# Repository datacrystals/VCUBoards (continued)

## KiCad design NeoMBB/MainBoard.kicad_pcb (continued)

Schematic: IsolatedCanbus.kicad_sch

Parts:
C44, C50, C51, C53: 100nF; C_1210_3225Metric_Pad1.33x2.70mm_HandSolder
C45, C49: 22pF; C_1210_3225Metric_Pad1.33x2.70mm_HandSolder
C46, C47, C48, C52: 10uF; C_1210_3225Metric_Pad1.33x2.70mm_HandSolder
C54, C55, C56: 22pF; C_1210_3225Metric_Pad1.33x2.70mm_HandSolder; not fitted
FL4: ACT45B-101-2P-TL003; ACT45B1012PTL003; Mouser Part Number 810-ACT45B1012PTL003
IC7: MCP2515-e_ST; SOP65P640X120-20N; Mouser Part Number 579-MCP2515-E/ST
IC8: ISO1042BDWVR; SOIC127P1150X280-8N; Mouser Part Number 595-ISO1042BDWVR
PS6: RKE-1205S_H; RKE1205SH; Mouser Part Number 919-RKE-1205S/H
R14: 4.7k; R_1210_3225Metric_Pad1.30x2.65mm_HandSolder
R15: 120; R_1210_3225Metric_Pad1.30x2.65mm_HandSolder
Y4: 8MHz; Crystal_HC49-4H_Vertical

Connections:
/+3.3V_A: C44.1, C46.2, C48.1, C51.1, IC7.20 (VDD), IC8.1 (VCC1), R14.2; also elsewhere on the board
/+12V_A: C47.1, C50.1, PS6.1 (+VIN); also elsewhere on the board
/CAN0_GND_E: C52.2, C53.1, C54.1, C55.2, IC8.5 (GND2), PS6.5 (-VOUT); also elsewhere on the board
/Control/CAN1_CS: IC7.18 (~CS); also elsewhere on the board
/Control/CAN1_INT: IC7.13 (~INT); also elsewhere on the board
/Control/CAN_SPI_RX: IC7.17 (SO); also elsewhere on the board
/Control/CAN_SPI_SCK: IC7.14 (SCK); also elsewhere on the board
/Control/CAN_SPI_TX: IC7.16 (SI); also elsewhere on the board
/Control/Isolated Canbus Module/CAN_JUMPER_B: R15.1; also elsewhere on the board
/DIAG_GND: C44.2, C45.2, C46.1, C47.2, C48.2, C49.2, C50.2, C51.2, IC7.10 (VSS), IC8.4 (GND1), PS6.2 (-VIN); also elsewhere on the board
/IO_CAN0_HIGH_E: C54.2, C56.1, FL4.4; also elsewhere on the board
/IO_CAN0_LOW_E: C55.1, C56.2, FL4.3, R15.2; also elsewhere on the board
/OUTPUT_CAN0_+5V_E: C52.1, C53.2, IC8.8 (VCC2), PS6.7 (+VOUT); also elsewhere on the board
unnamed: C49.1, IC7.9 (OSC1), Y4.2
unnamed: C45.1, IC7.8 (OSC2), Y4.1
unnamed: IC7.2 (RXCAN), IC8.3 (RXD)
unnamed: IC7.1 (TXCAN), IC8.2 (TXD)
unnamed: IC7.19 (~RESET), R14.1
unnamed: FL4.1, IC8.7 (CANH)
unnamed: FL4.2, IC8.6 (CANL)

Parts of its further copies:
C1, C7, C8, C10, C14, C20, C21, C23, C31, C37, C38, C40: 100nF; C_1210_3225Metric_Pad1.33x2.70mm_HandSolder
C2, C6, C15, C19, C32, C36: 22pF; C_1210_3225Metric_Pad1.33x2.70mm_HandSolder
C3, C4, C5, C9, C16, C17, C18, C22, C33, C34, C35, C39: 10uF; C_1210_3225Metric_Pad1.33x2.70mm_HandSolder
C11, C12, C13, C24, C25, C26, C41, C42, C43: 22pF; C_1210_3225Metric_Pad1.33x2.70mm_HandSolder; not fitted
FL1, FL2, FL3: ACT45B-101-2P-TL003; ACT45B1012PTL003; Mouser Part Number 810-ACT45B1012PTL003
IC1, IC3, IC5: MCP2515-e_ST; SOP65P640X120-20N; Mouser Part Number 579-MCP2515-E/ST
IC2, IC4, IC6: ISO1042BDWVR; SOIC127P1150X280-8N; Mouser Part Number 595-ISO1042BDWVR
PS2, PS3, PS5: RKE-1205S_H; RKE1205SH; Mouser Part Number 919-RKE-1205S/H
R1, R3, R12: 4.7k; R_1210_3225Metric_Pad1.30x2.65mm_HandSolder
R2, R4, R13: 120; R_1210_3225Metric_Pad1.30x2.65mm_HandSolder
Y1, Y2, Y3: 8MHz; Crystal_HC49-4H_Vertical

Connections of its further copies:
/+3.3V_A: C1.1, C3.2, C5.1, C8.1, C14.1, C16.2, C18.1, C21.1, C31.1, C33.2, C35.1, C38.1, IC1.20 (VDD), IC2.1 (VCC1), IC3.20 (VDD), IC4.1 (VCC1), IC5.20 (VDD), IC6.1 (VCC1), R1.2, R3.2, R12.2; also elsewhere on the board
/+12V_A: C4.1, C7.1, C17.1, C20.1, C34.1, C37.1, PS2.1 (+VIN), PS3.1 (+VIN), PS5.1 (+VIN); also elsewhere on the board
/CAN1_GND_F: C39.2, C40.1, C41.1, C42.2, IC6.5 (GND2), PS5.5 (-VOUT); also elsewhere on the board
/CAN2_+5V_G: C22.1, C23.2, IC4.8 (VCC2), PS3.7 (+VOUT); also elsewhere on the board
/CAN2_GND_G: C22.2, C23.1, C24.1, C25.2, IC4.5 (GND2), PS3.5 (-VOUT); also elsewhere on the board
/Control/CAN2_CS: IC5.18 (~CS); also elsewhere on the board
/Control/CAN2_INT: IC5.13 (~INT); also elsewhere on the board
/Control/CAN3_CS: IC3.18 (~CS); also elsewhere on the board
/Control/CAN3_INT: IC3.13 (~INT); also elsewhere on the board
/Control/CAN4_CS: IC1.18 (~CS); also elsewhere on the board
/Control/CAN4_INT: IC1.13 (~INT); also elsewhere on the board
/Control/CAN_SPI_RX: IC1.17 (SO), IC3.17 (SO), IC5.17 (SO); also elsewhere on the board
/Control/CAN_SPI_SCK: IC1.14 (SCK), IC3.14 (SCK), IC5.14 (SCK); also elsewhere on the board
/Control/CAN_SPI_TX: IC1.16 (SI), IC3.16 (SI), IC5.16 (SI); also elsewhere on the board
/Control/Isolated Canbus Module1/CAN_5V: C39.1, C40.2, IC6.8 (VCC2), PS5.7 (+VOUT)
/Control/Isolated Canbus Module1/CAN_JUMPER_B: R13.1; also elsewhere on the board
/Control/Isolated Canbus Module2/CAN_JUMPER_B: R4.1; also elsewhere on the board
/Control/Isolated Canbus Module3/CAN_5V: C9.1, C10.2, IC2.8 (VCC2), PS2.7 (+VOUT)
/Control/Isolated Canbus Module3/CAN_JUMPER_B: R2.1; also elsewhere on the board
/DIAG_GND: C1.2, C2.2, C3.1, C4.2, C5.2, C6.2, C7.2, C8.2, C14.2, C15.2, C16.1, C17.2, C18.2, C19.2, C20.2, C21.2, C31.2, C32.2, C33.1, C34.2, C35.2, C36.2, C37.2, C38.2, IC1.10 (VSS), IC2.4 (GND1), IC3.10 (VSS), IC4.4 (GND1), IC5.10 (VSS), IC6.4 (GND1), PS2.2 (-VIN), PS3.2 (-VIN), PS5.2 (-VIN); also elsewhere on the board
/IO_CAN1_HIGH_F: C41.2, C43.1, FL3.4; also elsewhere on the board
/IO_CAN1_LOW_F: C42.1, C43.2, FL3.3, R13.2; also elsewhere on the board
/IO_CAN2_HIGH_G: C24.2, C26.1, FL2.4; also elsewhere on the board
/IO_CAN2_LOW_G: C25.1, C26.2, FL2.3, R4.2; also elsewhere on the board
/IO_MOTOR_CONTR_CAN_HIGH_C: C11.2, C13.1, FL1.4; also elsewhere on the board
/IO_MOTOR_CONTR_CAN_LOW_C: C12.1, C13.2, FL1.3, R2.2; also elsewhere on the board
/SEVCON_GND_C: C9.2, C10.1, C11.1, C12.2, IC2.5 (GND2), PS2.5 (-VOUT); also elsewhere on the board
unnamed: C6.1, IC1.9 (OSC1), Y1.2
unnamed: C2.1, IC1.8 (OSC2), Y1.1
unnamed: IC1.2 (RXCAN), IC2.3 (RXD)
unnamed: IC1.1 (TXCAN), IC2.2 (TXD)
unnamed: IC1.19 (~RESET), R1.1
unnamed: FL1.1, IC2.7 (CANH)
unnamed: FL1.2, IC2.6 (CANL)
unnamed: C19.1, IC3.9 (OSC1), Y2.2
unnamed: C15.1, IC3.8 (OSC2), Y2.1
unnamed: IC3.2 (RXCAN), IC4.3 (RXD)
unnamed: IC3.1 (TXCAN), IC4.2 (TXD)
unnamed: IC3.19 (~RESET), R3.1
unnamed: FL2.1, IC4.7 (CANH)
unnamed: FL2.2, IC4.6 (CANL)
unnamed: C36.1, IC5.9 (OSC1), Y3.2
unnamed: C32.1, IC5.8 (OSC2), Y3.1
unnamed: IC5.2 (RXCAN), IC6.3 (RXD)
unnamed: IC5.1 (TXCAN), IC6.2 (TXD)
unnamed: IC5.19 (~RESET), R12.1
unnamed: FL3.1, IC6.7 (CANH)
unnamed: FL3.2, IC6.6 (CANL)

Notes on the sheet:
Isolated Canbus Power Supply
Close Jumper if terminating node

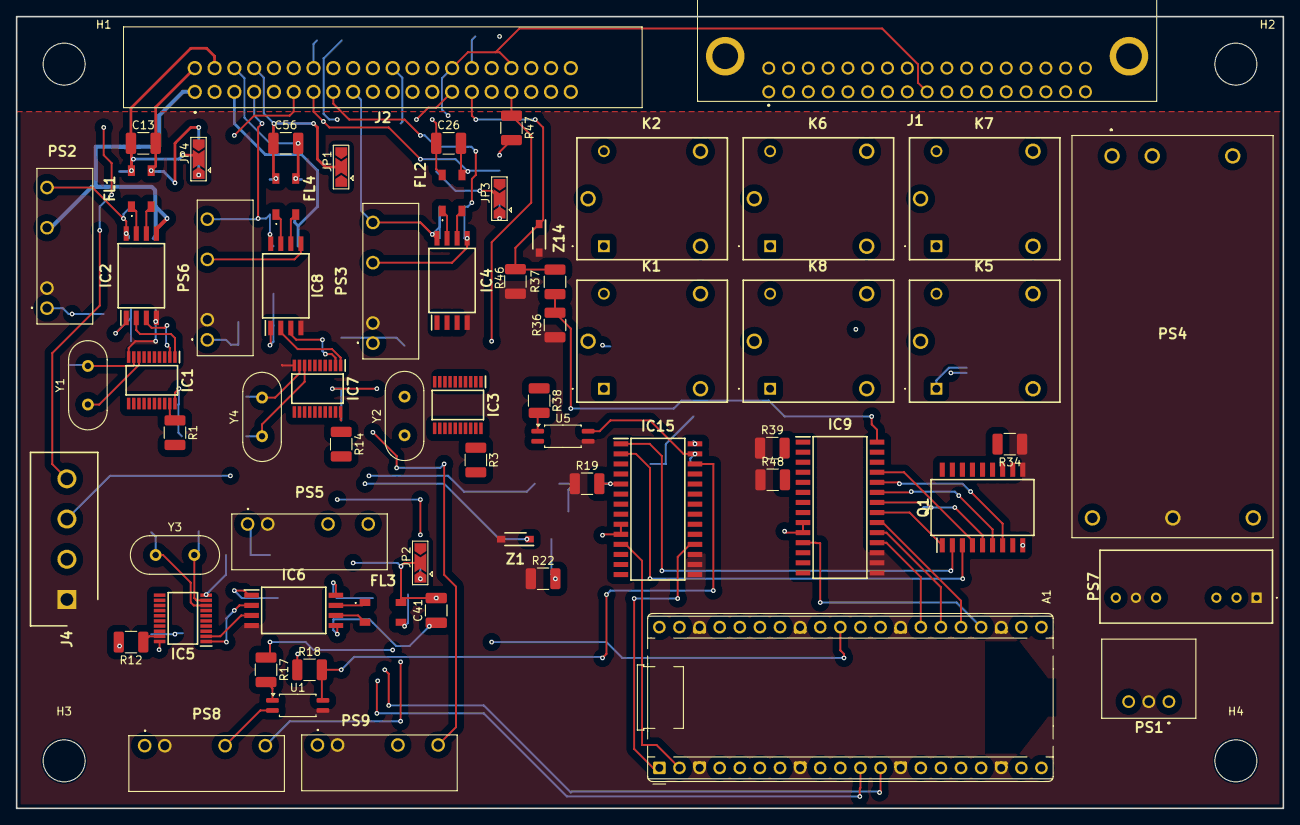
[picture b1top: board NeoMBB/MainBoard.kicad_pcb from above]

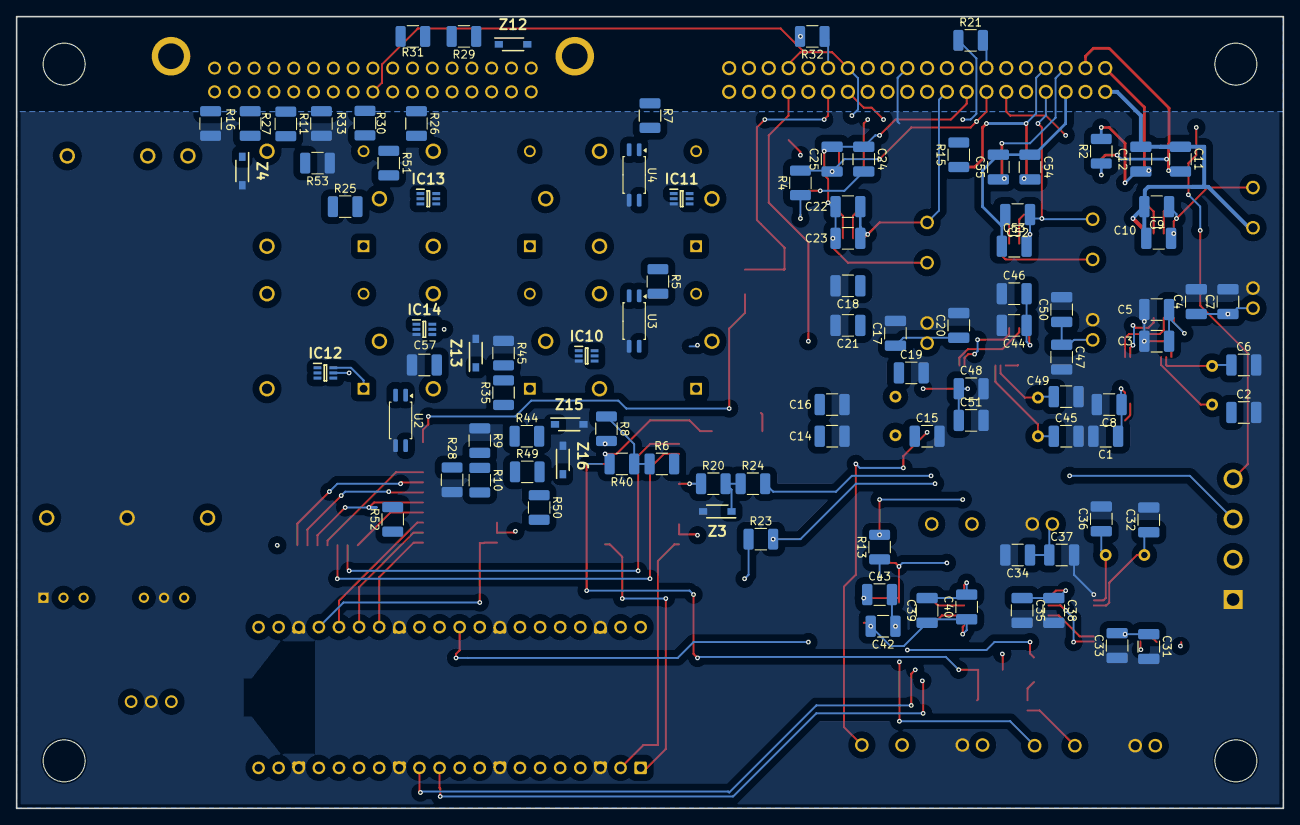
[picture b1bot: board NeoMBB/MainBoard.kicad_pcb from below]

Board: 6 copper layers, 160.0 x 100.0 mm, 167 parts (97 on the bottom side), 161 nets.

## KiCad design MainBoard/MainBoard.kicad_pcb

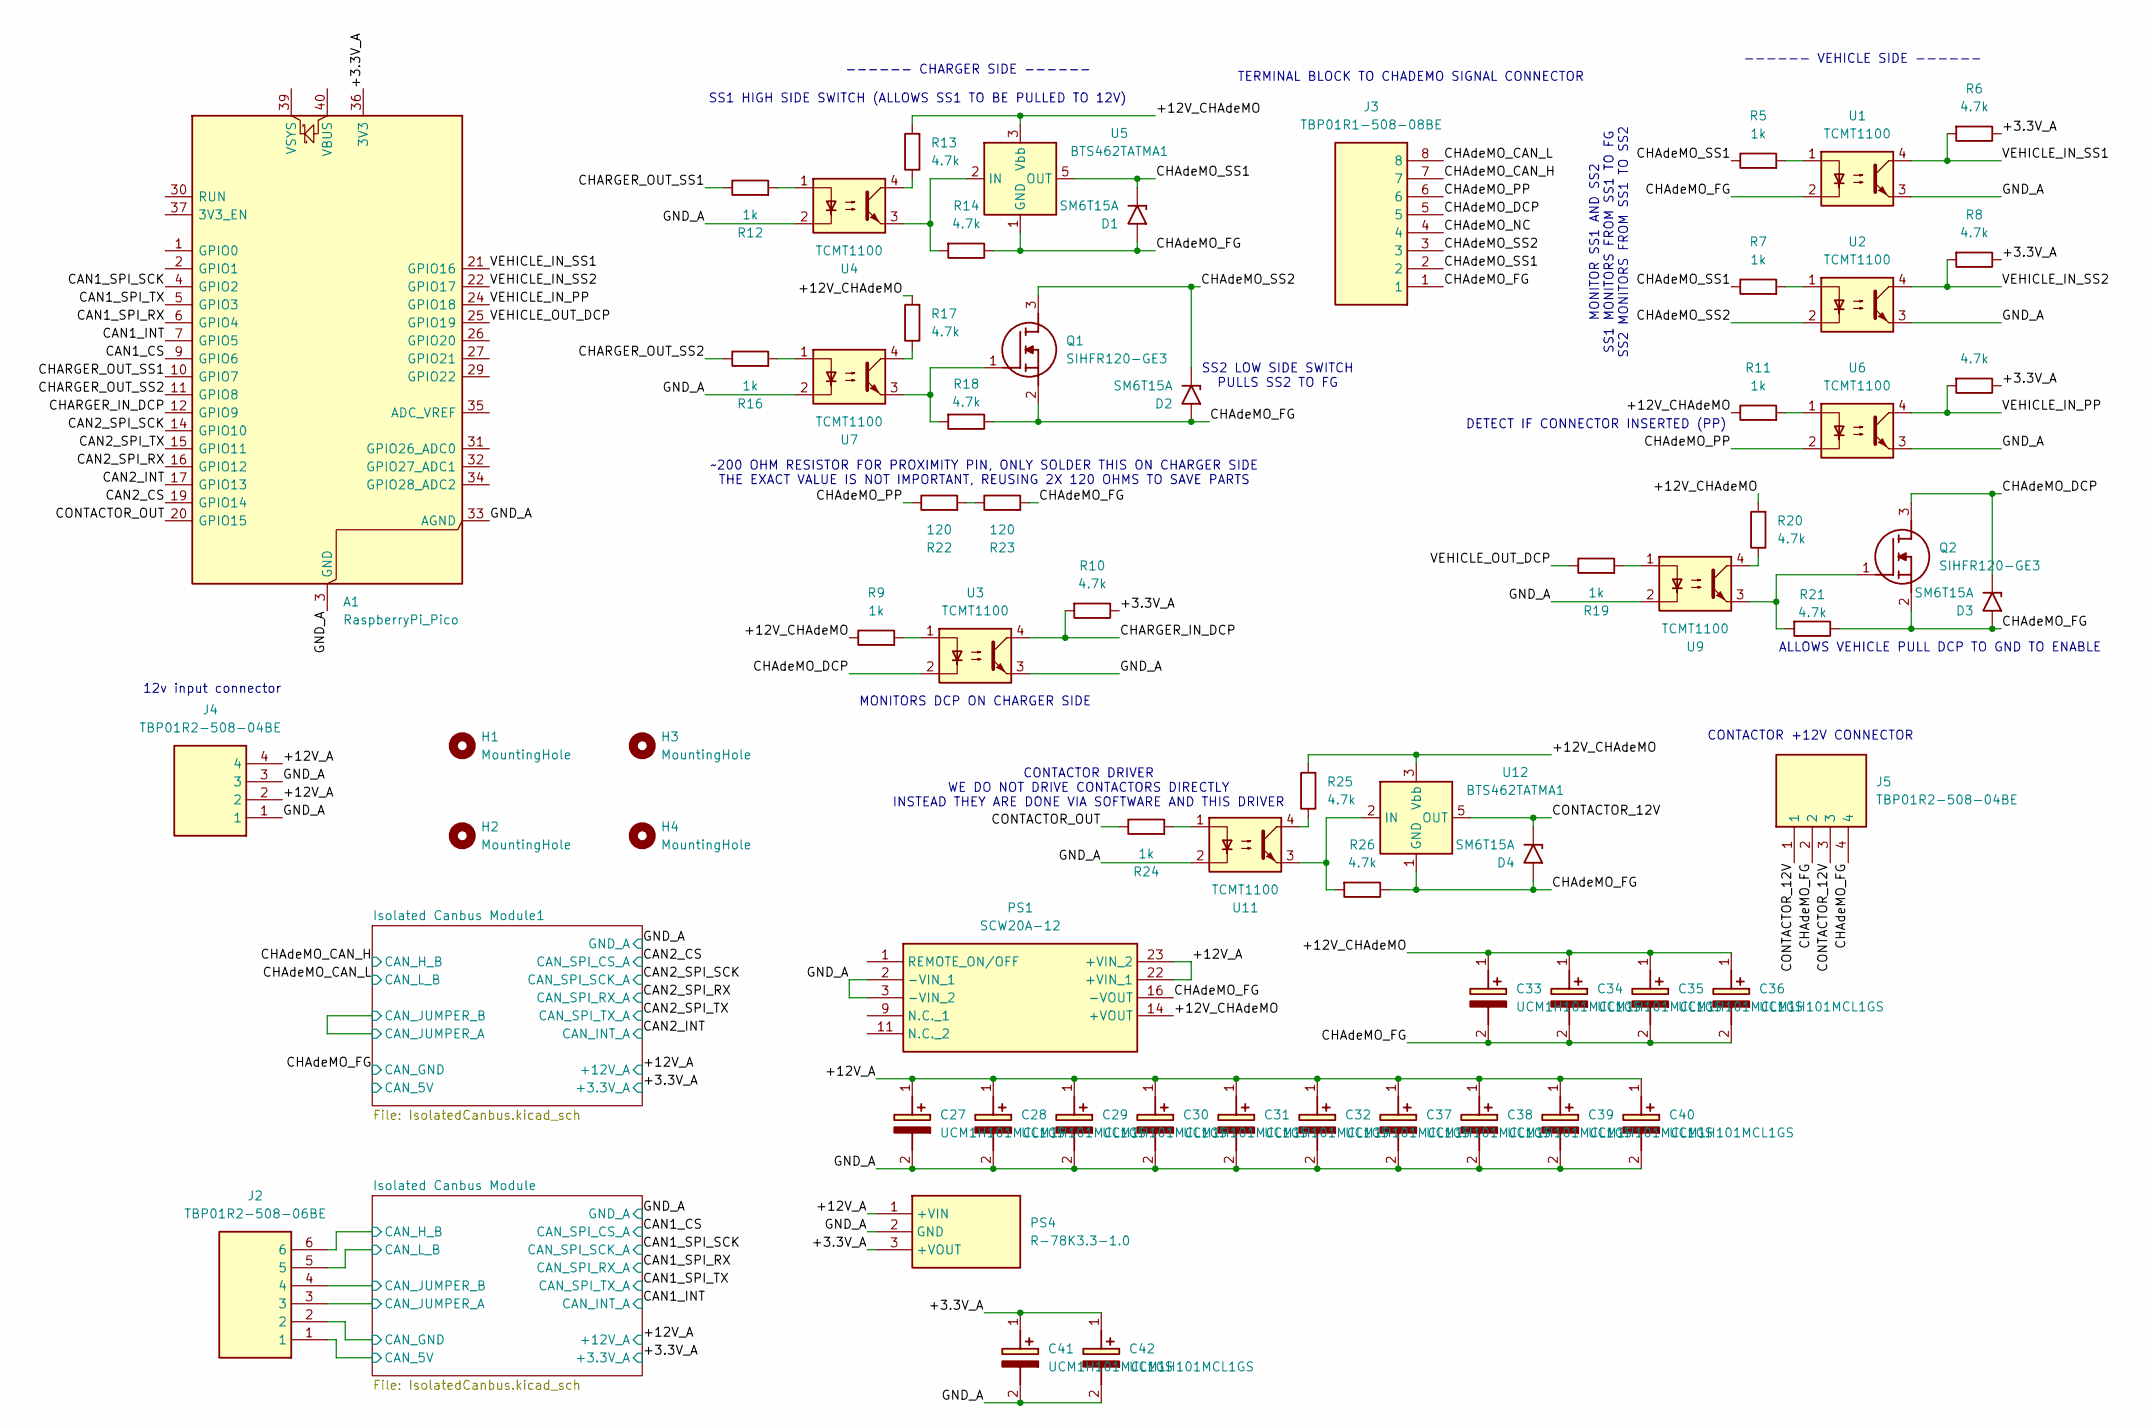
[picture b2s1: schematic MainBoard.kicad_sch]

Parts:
A1: RaspberryPi_Pico; RaspberryPi_Pico_Common_Unspecified
C27, C28, C29, C30, C31, C32, C33, C34, C35, C36, C37, C38, C39, C40, C41, C42: UCM1H101MCL1GS; CAPAE660X800N; Mouser Part Number 647-UCM1H101MCL1GS
D1, D2, D3, D4: SM6T15A; D_SMB
H1, H2, H3, H4: MountingHole; MountingHole_5.3mm_M5
J2: TBP01R2-508-06BE; TBP01R250806BE; Mouser Part Number 490-TBP01R2-508-06BE
J3: TBP01R1-508-08BE; SHDR8W100P0X508_1X8_4224X1200X890P; Mouser Part Number 490-TBP01R1-508-08BE
J4, J5: TBP01R2-508-04BE; SHDR4W100P0X508_1X4_2192X850X1200P; Mouser Part Number 490-TBP01R2-508-04BE
PS1: SCW20A-12; SCW20A12; Mouser Part Number 709-SCW20A-15
PS4: R-78K3.3-1.0; R78K3310; Mouser Part Number 919-R-78K3.3-1.0
Q1, Q2: SIHFR120-GE3; SIHFR120GE3; Mouser Part Number 78-SIHFR120-GE3
R5, R7, R9, R11, R12, R16, R19, R24: 1k; R_1210_3225Metric_Pad1.30x2.65mm_HandSolder
R6, R8, R10, R13, R14, R15, R17, R18, R20, R21, R25, R26: 4.7k; R_1210_3225Metric_Pad1.30x2.65mm_HandSolder
R22, R23: 120; R_1210_3225Metric_Pad1.30x2.65mm_HandSolder
U1, U2, U3, U4, U6, U7, U9, U11: TCMT1100; SOP-4_4.4x2.6mm_P1.27mm
U5, U12: BTS462TATMA1; TO-252-4

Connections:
/+3.3V_A: A1.36 (3V3), C41.1 (+), C42.1 (+), PS4.3 (+VOUT), R6.1, R8.1, R10.1, R15.1; also elsewhere on the board
/+12V_A: C27.1 (+), C28.1 (+), C29.1 (+), C30.1 (+), C31.1 (+), C32.1 (+), C37.1 (+), C38.1 (+), C39.1 (+), C40.1 (+), J4.2, J4.4, PS1.22 (+VIN_1), PS1.23 (+VIN_2), PS4.1 (+VIN); also elsewhere on the board
/+12V_CHAdeMO: C33.1 (+), C34.1 (+), C35.1 (+), C36.1 (+), PS1.14 (+VOUT), R9.1, R11.1, R13.2, R17.2, R20.2, R25.2, U5.3 (Vbb), U12.3 (Vbb)
/CAN1_CS: A1.9 (GPIO6); also elsewhere on the board
/CAN1_INT: A1.7 (GPIO5); also elsewhere on the board
/CAN1_SPI_RX: A1.6 (GPIO4); also elsewhere on the board
/CAN1_SPI_SCK: A1.4 (GPIO2); also elsewhere on the board
/CAN1_SPI_TX: A1.5 (GPIO3); also elsewhere on the board
/CAN2_CS: A1.19 (GPIO14); also elsewhere on the board
/CAN2_INT: A1.17 (GPIO13); also elsewhere on the board
/CAN2_SPI_RX: A1.16 (GPIO12); also elsewhere on the board
/CAN2_SPI_SCK: A1.14 (GPIO10); also elsewhere on the board
/CAN2_SPI_TX: A1.15 (GPIO11); also elsewhere on the board
/CHARGER_IN_DCP: A1.12 (GPIO9), R10.2, U3.4
/CHARGER_OUT_SS1: A1.10 (GPIO7), R12.1
/CHARGER_OUT_SS2: A1.11 (GPIO8), R16.1
/CHAdeMO_CAN_H: J3.7; also elsewhere on the board
/CHAdeMO_CAN_L: J3.8; also elsewhere on the board
/CHAdeMO_DCP: D3.1 (A1), J3.5, Q2.3 (D), U3.2
/CHAdeMO_FG: C33.2 (-), C34.2 (-), C35.2 (-), C36.2 (-), D1.2 (A2), D2.2 (A2), D3.2 (A2), D4.2 (A2), J3.1, J5.2, J5.4, PS1.16 (-VOUT), Q1.2 (S), Q2.2 (S), R14.1, R18.1, R21.1, R23.2, R26.1, U1.2, U5.1 (GND), U12.1 (GND); also elsewhere on the board
/CHAdeMO_NC: J3.4
/CHAdeMO_PP: J3.6, R22.1, U6.2
/CHAdeMO_SS1: D1.1 (A1), J3.2, R5.1, R7.1, U5.5 (OUT)
/CHAdeMO_SS2: D2.1 (A1), J3.3, Q1.3 (D), U2.2
/CONTACTOR_12V: D4.1 (A1), J5.1, J5.3, U12.5 (OUT)
/CONTACTOR_OUT: A1.20 (GPIO15), R24.1
/GND_A: A1.3 (GND), A1.8 (GND), A1.13 (GND), A1.18 (GND), A1.23 (GND), A1.28 (GND), A1.33 (AGND), A1.38 (GND), C27.2 (-), C28.2 (-), C29.2 (-), C30.2 (-), C31.2 (-), C32.2 (-), C37.2 (-), C38.2 (-), C39.2 (-), C40.2 (-), C41.2 (-), C42.2 (-), J4.1, J4.3, PS1.2 (-VIN_1), PS1.3 (-VIN_2), PS4.2 (GND), U1.3, U2.3, U3.3, U4.2, U6.3, U7.2, U9.2, U11.2; also elsewhere on the board
/Isolated Canbus Module/CAN_5V: J2.1; also elsewhere on the board
/Isolated Canbus Module/CAN_GND: J2.2; also elsewhere on the board
/Isolated Canbus Module/CAN_H_B: J2.3, J2.6; also elsewhere on the board
/Isolated Canbus Module/CAN_JUMPER_B: J2.4; also elsewhere on the board
/Isolated Canbus Module/CAN_L_B: J2.5; also elsewhere on the board
/VEHICLE_IN_PP: A1.24 (GPIO18), R15.2, U6.4
/VEHICLE_IN_SS1: A1.21 (GPIO16), R6.2, U1.4
/VEHICLE_IN_SS2: A1.22 (GPIO17), R8.2, U2.4
/VEHICLE_OUT_DCP: A1.25 (GPIO19), R19.1
unnamed: Q1.1 (G), R18.2, U7.3
unnamed: Q2.1 (G), R21.2, U9.3
unnamed: R5.2, U1.1
unnamed: R7.2, U2.1
unnamed: R9.2, U3.1
unnamed: R11.2, U6.1
unnamed: R12.2, U4.1
unnamed: R13.1, U4.4
unnamed: R16.2, U7.1
unnamed: R17.1, U7.4
unnamed: R19.2, U9.1
unnamed: R20.1, U9.4
unnamed: R22.2, R23.1
unnamed: R24.2, U11.1
unnamed: R25.1, U11.4
unnamed: R14.2, U4.3, U5.2 (IN)
unnamed: R26.2, U11.3, U12.2 (IN)

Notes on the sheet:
------ CHARGER SIDE ------
CONTACTOR +12V CONNECTOR
CONTACTOR DRIVER WE DO NOT DRIVE CONTACTORS DIRECTLY INSTEAD THEY ARE DONE VIA SOFTWARE AND THIS DRIVER
DETECT IF CONNECTOR INSERTED (PP)
12v input connector
ALLOWS VEHICLE PULL DCP TO GND TO ENABLE
MONITOR SS1 AND SS2 SS1 MONITORS FROM SS1 TO FG SS2 MONITORS FROM SS1 TO SS2
------ VEHICLE SIDE ------
SS2 LOW SIDE SWITCH PULLS SS2 TO FG
SS1 HIGH SIDE SWITCH (ALLOWS SS1 TO BE PULLED TO 12V)
~200 OHM RESISTOR FOR PROXIMITY PIN, ONLY SOLDER THIS ON CHARGER SIDE THE EXACT VALUE IS NOT IMPORTANT, REUSING 2X 120 OHMS TO SAVE PARTS
TERMINAL BLOCK TO CHADEMO SIGNAL CONNECTOR
MONITORS DCP ON CHARGER SIDE

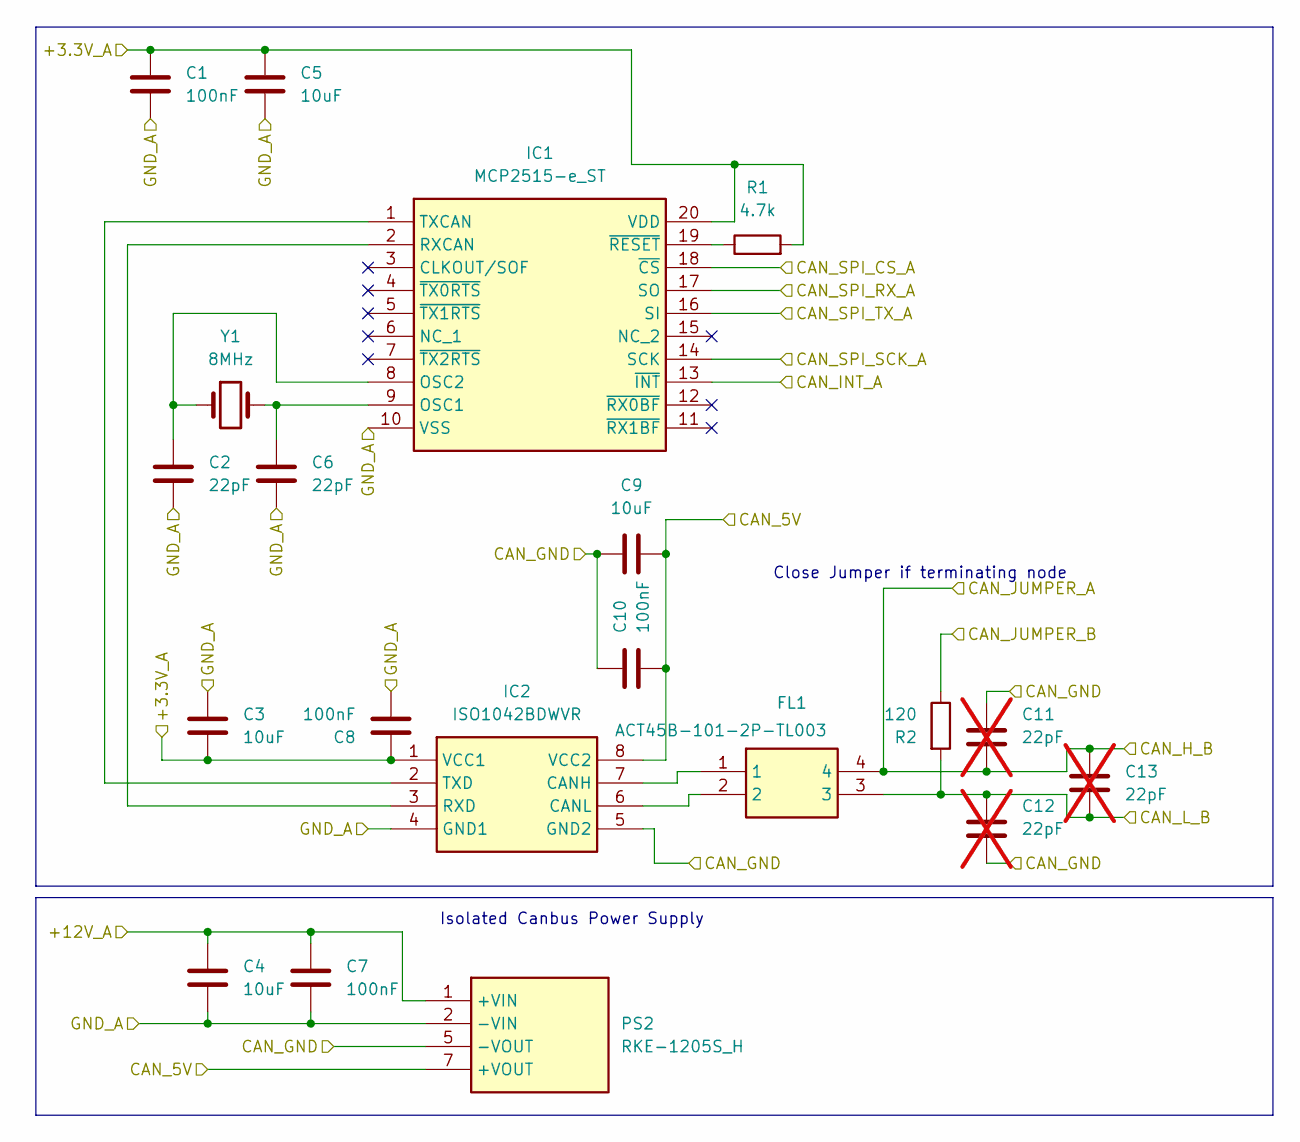
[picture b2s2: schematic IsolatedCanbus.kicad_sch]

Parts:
C1, C7, C8, C10: 100nF; C_1210_3225Metric_Pad1.33x2.70mm_HandSolder
C2, C6: 22pF; C_1210_3225Metric_Pad1.33x2.70mm_HandSolder
C3, C4, C5, C9: 10uF; C_1210_3225Metric_Pad1.33x2.70mm_HandSolder
C11, C12, C13: 22pF; C_1210_3225Metric_Pad1.33x2.70mm_HandSolder; not fitted
FL1: ACT45B-101-2P-TL003; ACT45B1012PTL003; Mouser Part Number 810-ACT45B1012PTL003
IC1: MCP2515-e_ST; SOP65P640X120-20N; Mouser Part Number 579-MCP2515-E/ST
IC2: ISO1042BDWVR; SOIC127P1150X280-8N; Mouser Part Number 595-ISO1042BDWVR
PS2: RKE-1205S_H; RKE1205SH; Mouser Part Number 919-RKE-1205S/H
R1: 4.7k; R_1210_3225Metric_Pad1.30x2.65mm_HandSolder
R2: 120; R_1210_3225Metric_Pad1.30x2.65mm_HandSolder
Y1: 8MHz; Crystal_HC49-4H_Vertical

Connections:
/+3.3V_A: C1.1, C3.2, C5.1, C8.1, IC1.20 (VDD), IC2.1 (VCC1), R1.2; also elsewhere on the board
/+12V_A: C4.1, C7.1, PS2.1 (+VIN); also elsewhere on the board
/CAN1_CS: IC1.18 (~CS); also elsewhere on the board
/CAN1_INT: IC1.13 (~INT); also elsewhere on the board
/CAN1_SPI_RX: IC1.17 (SO); also elsewhere on the board
/CAN1_SPI_SCK: IC1.14 (SCK); also elsewhere on the board
/CAN1_SPI_TX: IC1.16 (SI); also elsewhere on the board
/GND_A: C1.2, C2.2, C3.1, C4.2, C5.2, C6.2, C7.2, C8.2, IC1.10 (VSS), IC2.4 (GND1), PS2.2 (-VIN); also elsewhere on the board
/Isolated Canbus Module/CAN_5V: C9.1, C10.2, IC2.8 (VCC2), PS2.7 (+VOUT); also elsewhere on the board
/Isolated Canbus Module/CAN_GND: C9.2, C10.1, C11.1, C12.2, IC2.5 (GND2), PS2.5 (-VOUT); also elsewhere on the board
/Isolated Canbus Module/CAN_H_B: C11.2, C13.1, FL1.4; also elsewhere on the board
/Isolated Canbus Module/CAN_JUMPER_B: R2.1; also elsewhere on the board
/Isolated Canbus Module/CAN_L_B: C12.1, C13.2, FL1.3, R2.2; also elsewhere on the board
unnamed: C6.1, IC1.9 (OSC1), Y1.2
unnamed: C2.1, IC1.8 (OSC2), Y1.1
unnamed: IC1.2 (RXCAN), IC2.3 (RXD)
unnamed: IC1.1 (TXCAN), IC2.2 (TXD)
unnamed: IC1.19 (~RESET), R1.1
unnamed: FL1.1, IC2.7 (CANH)
unnamed: FL1.2, IC2.6 (CANL)

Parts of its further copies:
C14, C20, C21, C23: 100nF; C_1210_3225Metric_Pad1.33x2.70mm_HandSolder
C15, C19: 22pF; C_1210_3225Metric_Pad1.33x2.70mm_HandSolder
C16, C17, C18, C22: 10uF; C_1210_3225Metric_Pad1.33x2.70mm_HandSolder
C24, C25, C26: 22pF; C_1210_3225Metric_Pad1.33x2.70mm_HandSolder; not fitted
FL2: ACT45B-101-2P-TL003; ACT45B1012PTL003; Mouser Part Number 810-ACT45B1012PTL003
IC3: MCP2515-e_ST; SOP65P640X120-20N; Mouser Part Number 579-MCP2515-E/ST
IC4: ISO1042BDWVR; SOIC127P1150X280-8N; Mouser Part Number 595-ISO1042BDWVR
PS3: RKE-1205S_H; RKE1205SH; Mouser Part Number 919-RKE-1205S/H
R3: 4.7k; R_1210_3225Metric_Pad1.30x2.65mm_HandSolder
R4: 120; R_1210_3225Metric_Pad1.30x2.65mm_HandSolder
Y2: 8MHz; Crystal_HC49-4H_Vertical

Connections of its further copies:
/+3.3V_A: C14.1, C16.2, C18.1, C21.1, IC3.20 (VDD), IC4.1 (VCC1), R3.2; also elsewhere on the board
/+12V_A: C17.1, C20.1, PS3.1 (+VIN); also elsewhere on the board
/CAN2_CS: IC3.18 (~CS); also elsewhere on the board
/CAN2_INT: IC3.13 (~INT); also elsewhere on the board
/CAN2_SPI_RX: IC3.17 (SO); also elsewhere on the board
/CAN2_SPI_SCK: IC3.14 (SCK); also elsewhere on the board
/CAN2_SPI_TX: IC3.16 (SI); also elsewhere on the board
/CHAdeMO_CAN_H: C24.2, C26.1, FL2.4, R4.1; also elsewhere on the board
/CHAdeMO_CAN_L: C25.1, C26.2, FL2.3, R4.2; also elsewhere on the board
/CHAdeMO_FG: C22.2, C23.1, C24.1, C25.2, IC4.5 (GND2), PS3.5 (-VOUT); also elsewhere on the board
/GND_A: C14.2, C15.2, C16.1, C17.2, C18.2, C19.2, C20.2, C21.2, IC3.10 (VSS), IC4.4 (GND1), PS3.2 (-VIN); also elsewhere on the board
/Isolated Canbus Module1/CAN_5V: C22.1, C23.2, IC4.8 (VCC2), PS3.7 (+VOUT)
unnamed: C19.1, IC3.9 (OSC1), Y2.2
unnamed: C15.1, IC3.8 (OSC2), Y2.1
unnamed: IC3.2 (RXCAN), IC4.3 (RXD)
unnamed: IC3.1 (TXCAN), IC4.2 (TXD)
unnamed: IC3.19 (~RESET), R3.1
unnamed: FL2.1, IC4.7 (CANH)
unnamed: FL2.2, IC4.6 (CANL)

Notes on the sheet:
Isolated Canbus Power Supply
Close Jumper if terminating node

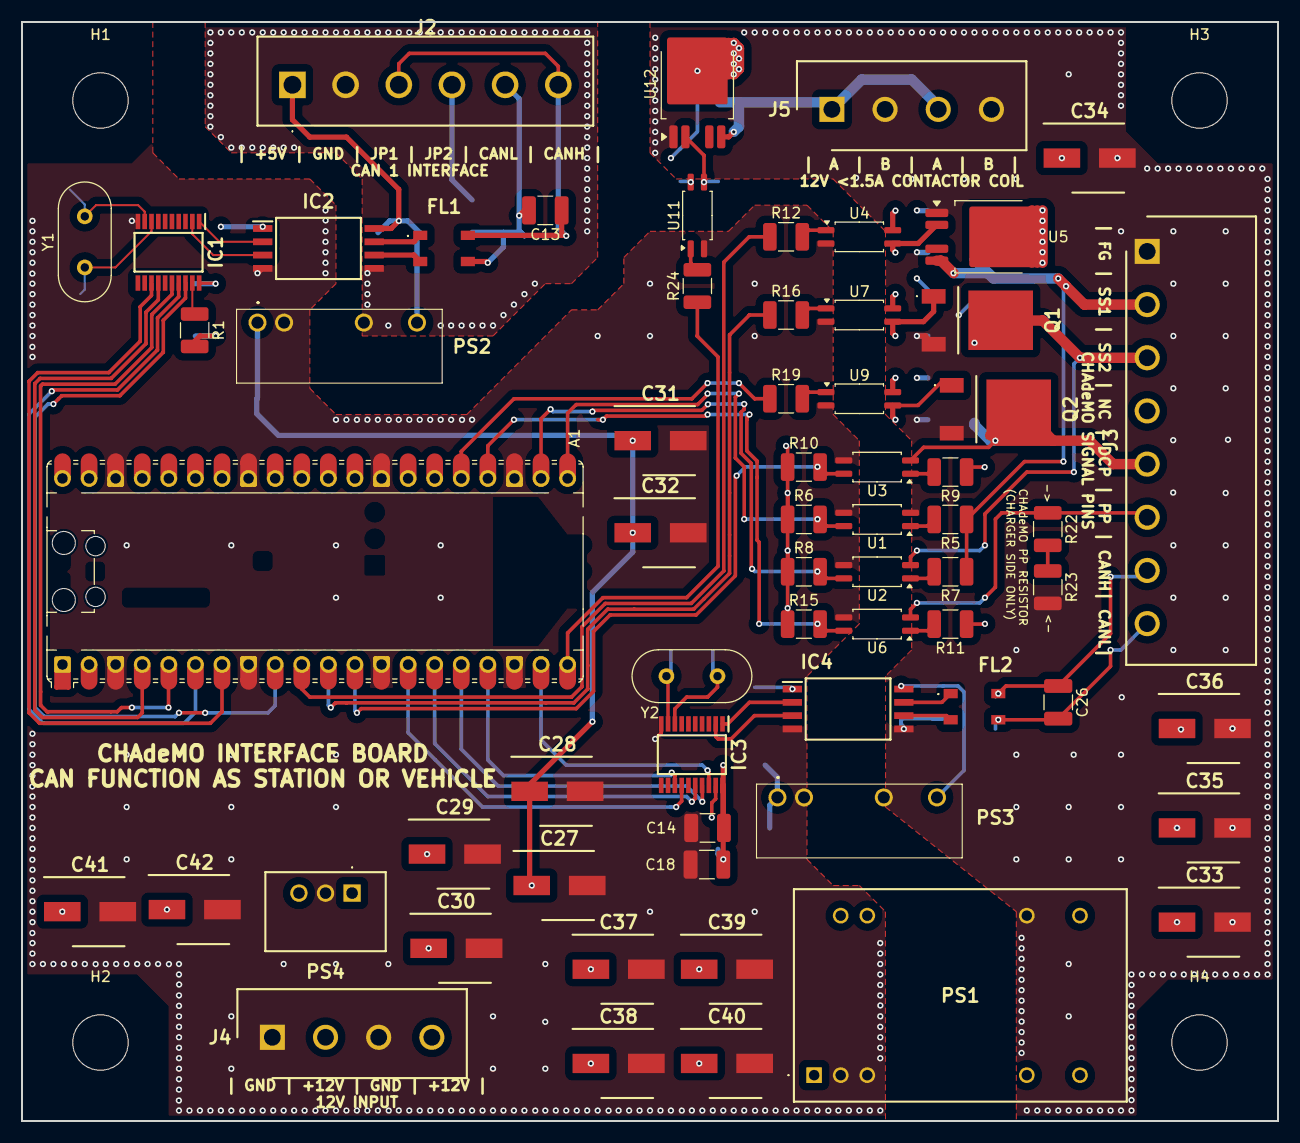
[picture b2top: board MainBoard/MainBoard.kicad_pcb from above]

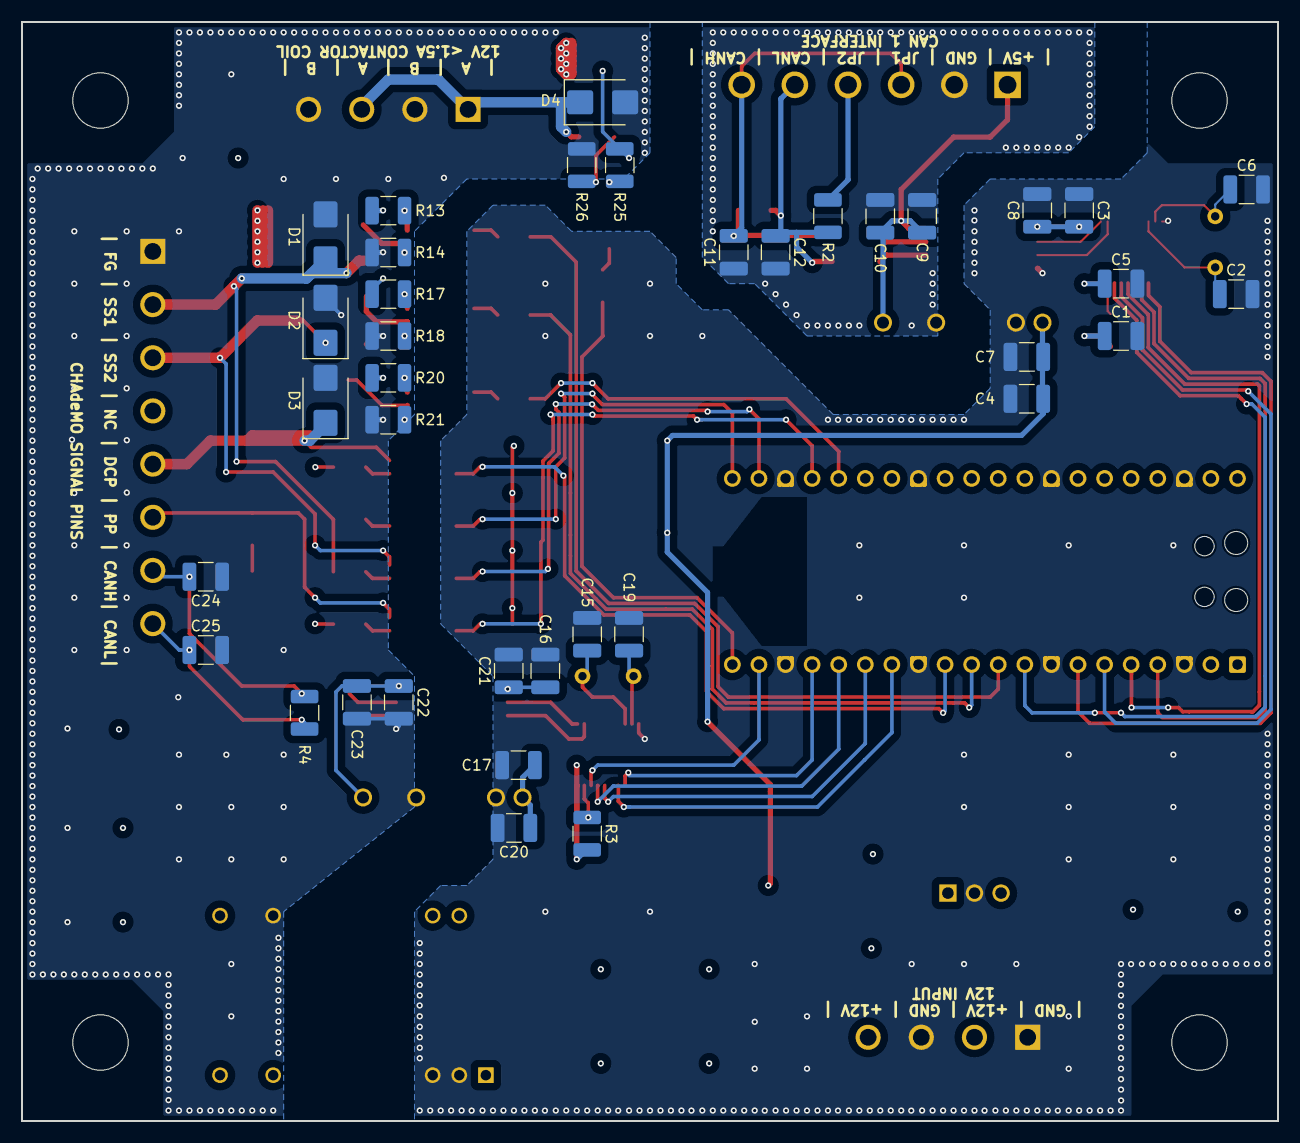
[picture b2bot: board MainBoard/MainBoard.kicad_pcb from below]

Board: 4 copper layers, 120.0 x 105.0 mm, 105 parts (37 on the bottom side), 67 nets.

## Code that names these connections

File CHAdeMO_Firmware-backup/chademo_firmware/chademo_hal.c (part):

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static const can_hw_config_t can_cfg[2] = {
    [HAL_CAN_CH1] = {
        .spi      = MCP2515_SPI_PORT,      /* spi0 */
        .pin_sck  = PIN_CAN1_SPI_SCK,      /* GPIO2 */
        .pin_tx   = PIN_CAN1_SPI_TX,       /* GPIO3 (MOSI) */
        .pin_rx   = PIN_CAN1_SPI_RX,       /* GPIO4 (MISO) */
        .pin_cs   = PIN_CAN1_CS,           /* GPIO6 */
        .pin_int  = PIN_CAN1_INT,          /* GPIO5 */
        .baud_hz  = MCP2515_SPI_BAUD_HZ    /* 10 MHz */
    },
    [HAL_CAN_CH2] = {
        .spi      = MCP2515_SPI_PORT_2,    /* spi1 */
        .pin_sck  = PIN_CAN2_SPI_SCK,      /* GPIO10 */
        .pin_tx   = PIN_CAN2_SPI_TX,       /* GPIO11 (MOSI) */
        .pin_rx   = PIN_CAN2_SPI_RX,       /* GPIO12 (MISO) */
        .pin_cs   = PIN_CAN2_CS,           /* GPIO14 */
        .pin_int  = PIN_CAN2_INT,          /* GPIO13 */
        .baud_hz  = MCP2515_SPI_BAUD_HZ_2  /* 10 MHz */
    }
};
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
void hal_gpio_init(void)
{
    /* ---- COMMON: Contactor driver (GPIO15) ----
     * CRITICAL SAFETY: Contactor MUST be OPEN on boot.
     * Initialize as output, driven LOW before anything else.
     */
    gpio_init(PIN_CONTACTOR_OUT);
    gpio_set_dir(PIN_CONTACTOR_OUT, GPIO_OUT);
    gpio_put(PIN_CONTACTOR_OUT, 0);  /* Contactor OPEN */

#if IS_STATION
    /* ---- CHARGER (EVSE) ROLE ----
     * Outputs: SS1 (GPIO7), SS2 (GPIO8) — active-HIGH via opto/SolidState
     * Input:  DCP (GPIO9) — active-HIGH from vehicle
     */
    gpio_init(PIN_OUT_SS1);
    gpio_set_dir(PIN_OUT_SS1, GPIO_OUT);
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
#else
    /* ---- VEHICLE ROLE ----
     * Inputs:  SS1 (GPIO16), SS2 (GPIO17), PP (GPIO18)
     * Output: DCP (GPIO19) — active-HIGH to charger
     */
    gpio_init(PIN_IN_SS1);
    gpio_set_dir(PIN_IN_SS1, GPIO_IN);
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
void hal_gpio_set_contactor(bool close)
{
    gpio_put(PIN_CONTACTOR_OUT, close ? 1 : 0);
}

bool hal_gpio_get_contactor(void)
{
    return (gpio_get(PIN_CONTACTOR_OUT) != 0);
}

#if IS_STATION
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
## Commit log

2026-05-05 sorta chademo?
2026-05-05 debugging now that can works, protocol neogtion fails
2026-05-05 vehicle side works
2026-05-05 lower voltage 300v now
2026-05-07 add mbb
2026-05-07 Station: inverted DCP detection, CAN reset on plug-in, TX buffer round-robin, no TX in IDLE, unplug monitor
    - DCP LOW = vehicle present (matches hardware inversion)
    - Global unplug monitor: DCP HIGH aborts to IDLE in any state
    - Stop CAN TX in IDLE to prevent bus error accumulation
    - Reset MCP2515 on plug detect to clear bus-off/error state
    - Round-robin TXB0/1/2 to avoid stuck buffers
    - Revert vehicle DCP (original code was correct)
2026-05-07 Chademo fw updates
2026-05-07 Add .gitignore, remove build artifacts, add station contactor GPIO control
    - Station contactor closes during PRECHARGE and stays closed in CHARGING
    - Station contactor opens during SHUTDOWN, FAULT_SHUTDOWN, CONTACTOR_OPEN, and unplug
    - Added .gitignore to prevent build artifacts and logs from being committed
    - Removed previously committed build/ directory, Archive.zip, and blinky_test.uf2
2026-05-07 Fix hardcoded STATION boot message to show actual build role
2026-05-07 Add role prefix to all log lines for clarity
    Every printf status line now prefixes with STATION or VEHICLE:
    - [STATION-STAT], [VEHICLE-STAT], [STATION-CAN], [VEHICLE-EVT], etc.
    - CHADEMO_LOG macro now includes role: [CHADEMO-STATION] / [CHADEMO-VEHICLE]
    - Fixed hardcoded boot message from prior commit to use FSM_ROLE_STR
2026-05-07 Fix station sim voltage: start at 0V, ramp only in PRECHARGE/CHARGING
    Station was falsely reporting 50V during INSULATION_TEST because the
    simulated voltage started at 50 for both roles. This triggered the
    'voltage present, possible weld' fault and prevented the station from
    ever reaching PRECHARGE to close its contactor.
    - Station sim_voltage is now 0 in IDLE through INSULATION_TEST
    - Ramps up during PRECHARGE/CHARGING as before
2026-05-07 Fix PRECHARGE logic and parameter persistence
    - Remove vehicle-side if(1) hack that bypassed voltage check in PRECHARGE
    - Lower CHADEMO_PRECHARGE_THRESHOLD_V from 50V to 10V for 50V bench test
    - Add voltage-matching guard to station PRECHARGE->CHARGING transition
    - Add voltage guard to vehicle PRECHARGE->CHARGING transition (defense-in-depth)
    - Speed up simulation voltage ramp from 1V to 5V per loop for snappier testing
    - Refresh battery/capability params every loop so they survive FSM resets
2026-05-13 Probed Zero wiring harness
2026-05-14 MBB Reverse engineering bs
2026-05-14 layout
2026-05-15 Update MBB Layout
